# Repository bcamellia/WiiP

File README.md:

# WiiP
Circuits designed for usage in a portable Wii.  
See https://creationsofchris.wordpress.com/ for blog posts and design decisions.  

## Overview:  
* TPS5432 based power regulator takes a 5V input and outputs 1V, 1.15V, and 3.3V at up to 3A.
* LM485 based amp includes headphone sensing and uses a digital potentiometer for volume control.
* MAX4886 to connect Wii HDMI video (converted using GCVideo) to external monitor.
* Case designed in sketchup, prints ok using ABS plastic.

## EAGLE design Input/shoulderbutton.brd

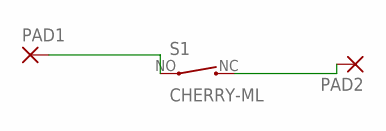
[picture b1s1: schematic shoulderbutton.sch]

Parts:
PAD1, PAD2: 2,15/1,0
S1: CHERRY-ML

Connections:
unnamed: PAD1.1, S1.NO (1)
unnamed: PAD2.1, S1.NC (2)

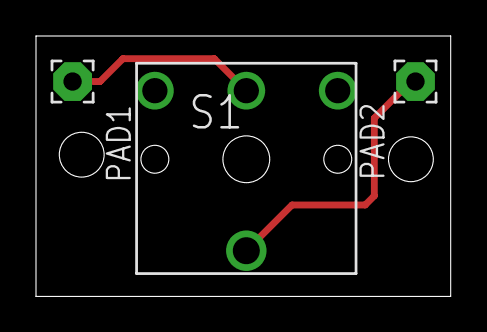
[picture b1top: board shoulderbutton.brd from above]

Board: 2 copper layers, 23.0 x 14.5 mm, 3 parts (0 on the bottom side), 2 nets.

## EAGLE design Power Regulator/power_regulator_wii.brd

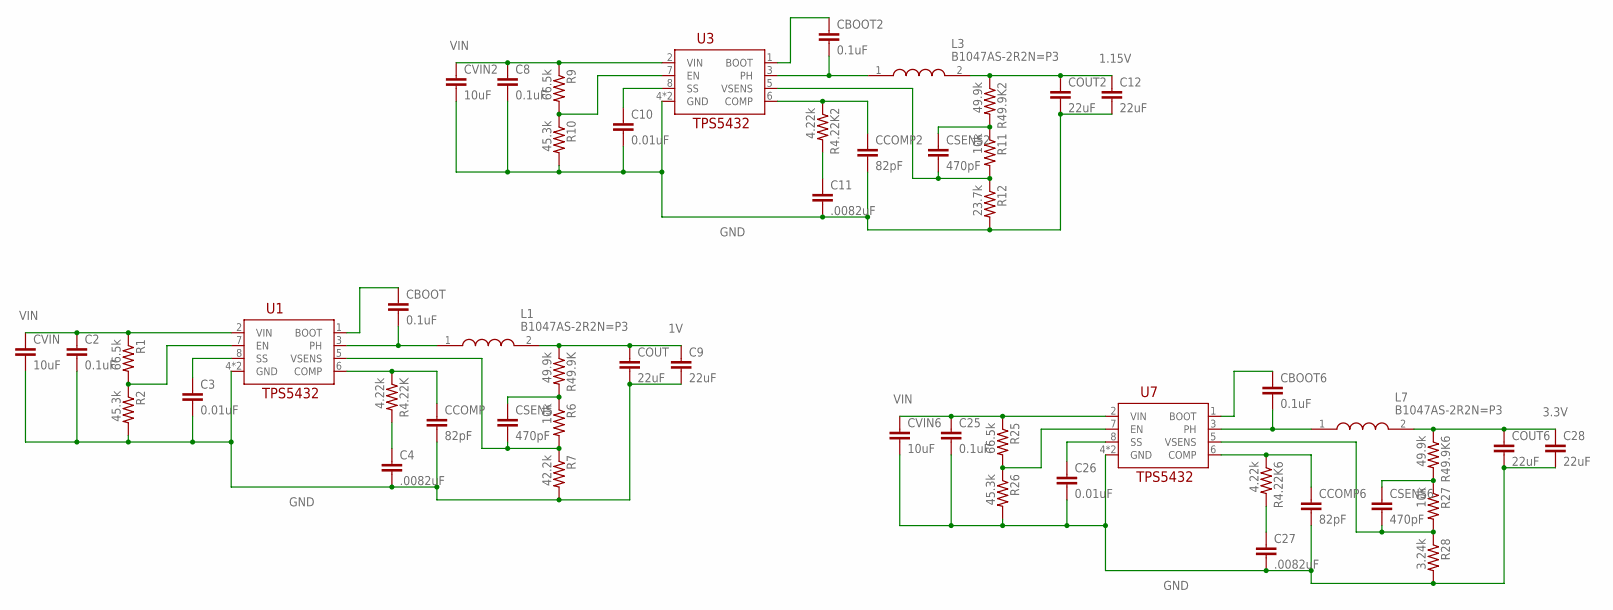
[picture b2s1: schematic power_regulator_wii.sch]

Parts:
C2, C8, C25: 0.1uF; C0603
C3, C10, C26: 0.01uF; C0603
C4, C11, C27: .0082uF; C0603
C9, C12, C28: 22uF; C0603
CBOOT, CBOOT2, CBOOT6: 0.1uF; C0603
CCOMP, CCOMP2, CCOMP6: 82pF; C0603
COUT, COUT2, COUT6: 22uF; C0603
CSENS, CSENS2, CSENS6: 470pF; C0603
CVIN, CVIN2, CVIN6: 10uF; C0603
L1, L3, L7: B1047AS-2R2N=P3; INDPM7474X500N
R1, R9, R25: 66.5k; R0603
R2, R10, R26: 45.3k; R0603
R4.22K, R4.22K2, R4.22K6: 4.22k; R0603
R6, R11, R27: 10k; R0603
R7: 42.2k; R0603
R12: 23.7k; R0603
R28: 3.24k; R0603
R49.9K, R49.9K2, R49.9K6: 49.9k; R0603
U1, U3, U7: TPS5432; SO-8

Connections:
1.15V: C12.1, COUT2.1, L3.2, R49.9K2.1
1V: C9.1, COUT.1, L1.2, R49.9K.1
3.3V: C28.1, COUT6.1, L7.2, R49.9K6.1
BOOT: CBOOT.1, U1.1 (BOOT)
BOOT2: CBOOT2.1, U3.1 (BOOT)
BOOT6: CBOOT6.1, U7.1 (BOOT)
COMP: CCOMP.1, R4.22K.1, U1.6 (COMP)
COMP2: CCOMP2.1, R4.22K2.1, U3.6 (COMP)
COMP6: CCOMP6.1, R4.22K6.1, U7.6 (COMP)
EN: R1.2, R2.1, U1.7 (EN)
EN2: R9.2, R10.1, U3.7 (EN)
EN6: R25.2, R26.1, U7.7 (EN)
GND: C2.2, C3.2, C4.2, C8.2, C9.2, C10.2, C11.2, C12.2, C25.2, C26.2, C27.2, C28.2, CCOMP.2, CCOMP2.2, CCOMP6.2, COUT.2, COUT2.2, COUT6.2, CVIN.2, CVIN2.2, CVIN6.2, R2.2, R7.2, R10.2, R12.2, R26.2, R28.2, U1.4 (GND), U1.PAD (GND), U3.4 (GND), U3.PAD (GND), U7.4 (GND), U7.PAD (GND)
unnamed: C11.1, R4.22K2.2
unnamed: CSENS2.1, R11.1, R49.9K2.2
unnamed: C4.1, R4.22K.2
unnamed: CSENS.1, R6.1, R49.9K.2
unnamed: C27.1, R4.22K6.2
unnamed: CSENS6.1, R27.1, R49.9K6.2
PH: CBOOT.2, L1.1, U1.3 (PH)
PH2: CBOOT2.2, L3.1, U3.3 (PH)
PH6: CBOOT6.2, L7.1, U7.3 (PH)
SS: C3.1, U1.8 (SS)
SS2: C10.1, U3.8 (SS)
SS6: C26.1, U7.8 (SS)
VIN: C2.1, C8.1, C25.1, CVIN.1, CVIN2.1, CVIN6.1, R1.1, R9.1, R25.1, U1.2 (VIN), U3.2 (VIN), U7.2 (VIN)
VSENS: CSENS.2, R6.2, R7.1, U1.5 (VSENS)
VSENS2: CSENS2.2, R11.2, R12.1, U3.5 (VSENS)
VSENS6: CSENS6.2, R27.2, R28.1, U7.5 (VSENS)

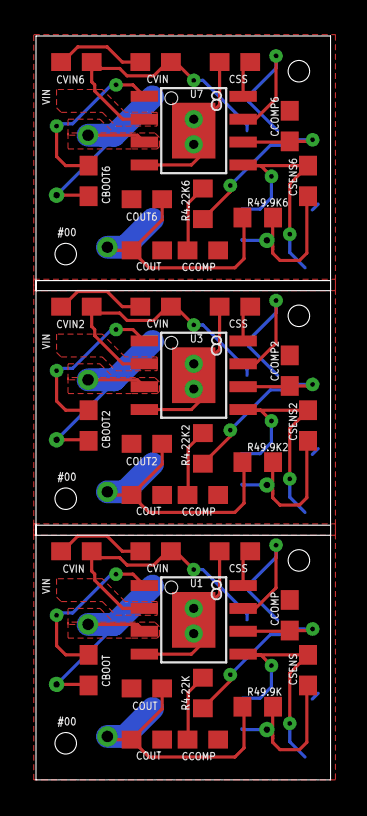
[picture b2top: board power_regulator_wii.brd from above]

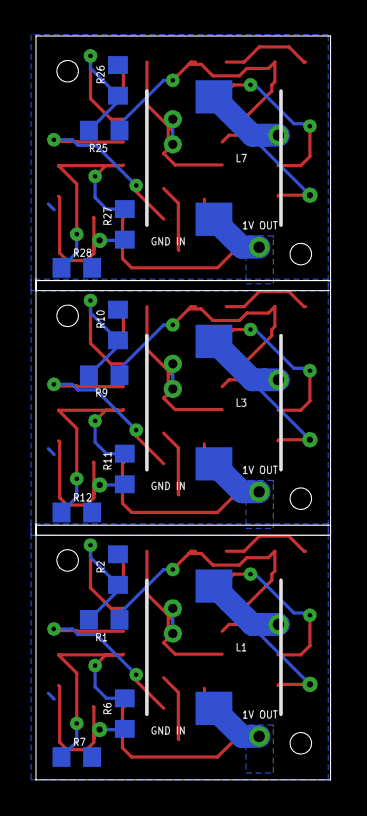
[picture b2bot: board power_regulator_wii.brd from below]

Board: 2 copper layers, 16.4 x 41.3 mm, 51 parts (15 on the bottom side), 29 nets.

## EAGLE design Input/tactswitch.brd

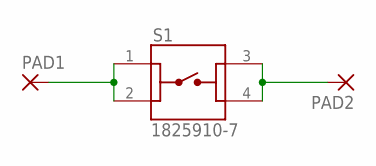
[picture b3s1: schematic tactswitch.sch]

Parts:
PAD1, PAD2: 2,15/1,0
S1: 1825910-7; SW_1825910-7

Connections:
unnamed: PAD1.1, S1.1, S1.2
unnamed: PAD2.1, S1.3, S1.4

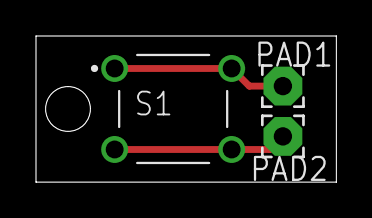
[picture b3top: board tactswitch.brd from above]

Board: 2 copper layers, 16.7 x 8.1 mm, 3 parts (0 on the bottom side), 2 nets.

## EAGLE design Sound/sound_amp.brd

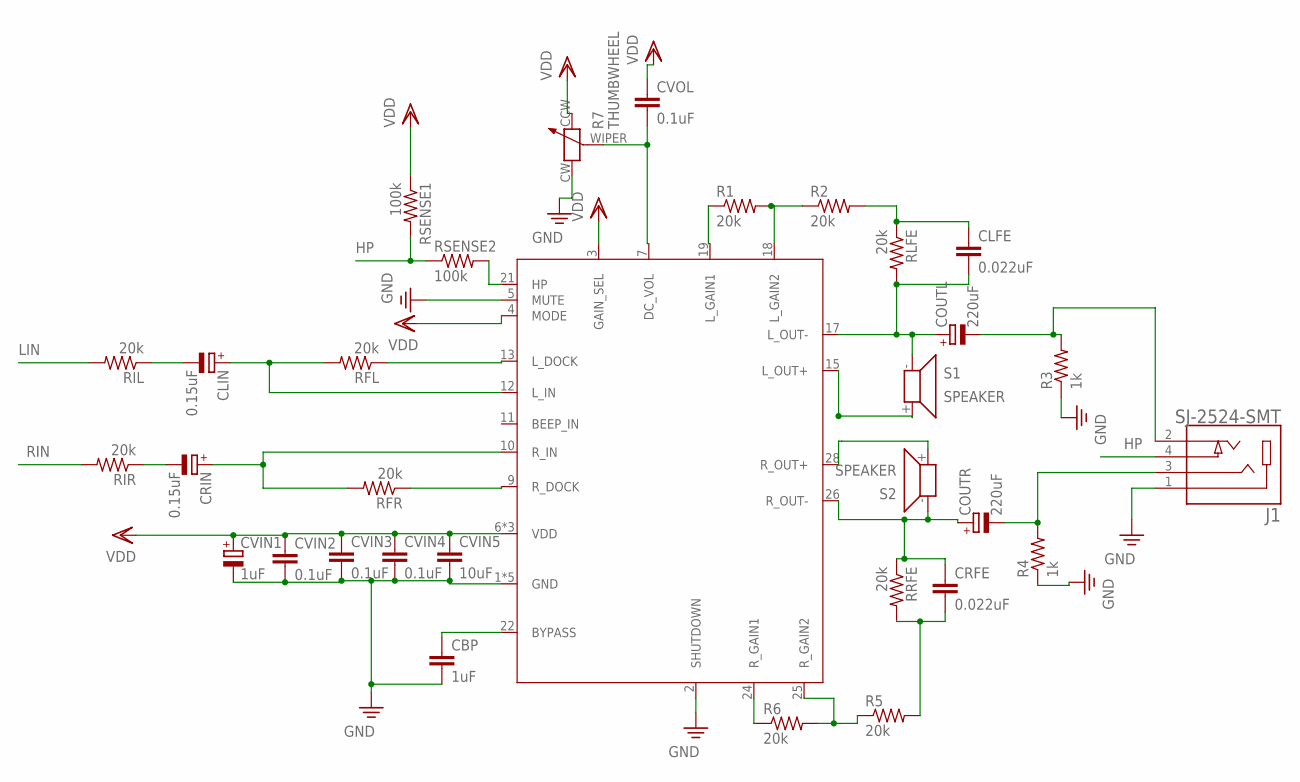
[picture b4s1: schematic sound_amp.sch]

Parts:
CBP: 1uF; C0603
CLFE: 0.022uF; C0603
CLIN: 0.15uF; B45181A
COUTL: 220uF; B45181A
COUTR: 220uF; B45181A
CRFE: 0.022uF; C0603
CRIN: 0.15uF; B45181A
CVIN1: 1uF; B45181A
CVIN2, CVIN3, CVIN4: 0.1uF; C0603
CVIN5: 10uF; C0603
CVOL: 0.1uF; C0603
J1: SJ-2524-SMT; CUI_SJ-2524-SMT
R1, R2, R5, R6: 20k; R0603
R3, R4: 1k; R0603
R7: THUMBWHEEL
RFL: 20k; R0603
RFR: 20k; R0603
RIL: 20k; R0603
RIR: 20k; R0603
RLFE: 20k; R0603
RRFE: 20k; R0603
RSENSE1, RSENSE2: 100k; R0603
S1, S2: SPEAKER; SIGNALOUT
U1: LM4835; TSSOP-28

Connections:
BYPASS: CBP.1, U1.22 (BYPASS)
GND: CBP.2, CVIN1.-, CVIN2.2, CVIN3.2, CVIN4.2, CVIN5.2, J1.1, R3.1, R4.1, R7.CW, U1.1 (GND), U1.2 (SHUTDOWN), U1.5 (MUTE), U1.8 (GND), U1.14 (GND), U1.20 (GND), U1.23 (GND)
HP: J1.4, RSENSE1.2, RSENSE2.1
LDOCK: RFL.1, U1.13 (L_DOCK)
LIN: RIL.2
LOUT+: S1.+, U1.15 (L_OUT+)
LOUT-: CLFE.2, COUTL.+, RLFE.2, S1.-, U1.17 (L_OUT-)
unnamed: CLIN.+, RFL.2, U1.12 (L_IN)
unnamed: CRIN.+, RFR.2, U1.10 (R_IN)
unnamed: CRIN.-, RIR.1
unnamed: CLIN.-, RIL.1
unnamed: CVOL.2, R7.WIPER, U1.7 (DC_VOL)
unnamed: RSENSE2.2, U1.21 (HP)
unnamed: CLFE.1, R2.2, RLFE.1
unnamed: R1.2, R2.1, U1.18 (L_GAIN2)
unnamed: R1.1, U1.19 (L_GAIN1)
unnamed: COUTL.-, J1.2, R3.2
unnamed: COUTR.-, J1.3, R4.2
unnamed: CRFE.2, R5.2, RRFE.2
RDOCK: RFR.1, U1.9 (R_DOCK)
RGAIN1: R6.1, U1.24 (R_GAIN1)
RGAIN2: R5.1, R6.2, U1.25 (R_GAIN2)
RIN: RIR.2
ROUT+: S2.+, U1.28 (R_OUT+)
ROUT-: COUTR.+, CRFE.1, RRFE.1, S2.-, U1.26 (R_OUT-)
VDD: CVIN1.+, CVIN2.1, CVIN3.1, CVIN4.1, CVIN5.1, CVOL.1, R7.CCW, RSENSE1.1, U1.3 (GAIN_SEL), U1.4 (MODE), U1.6 (VDD), U1.16 (VDD), U1.27 (VDD)

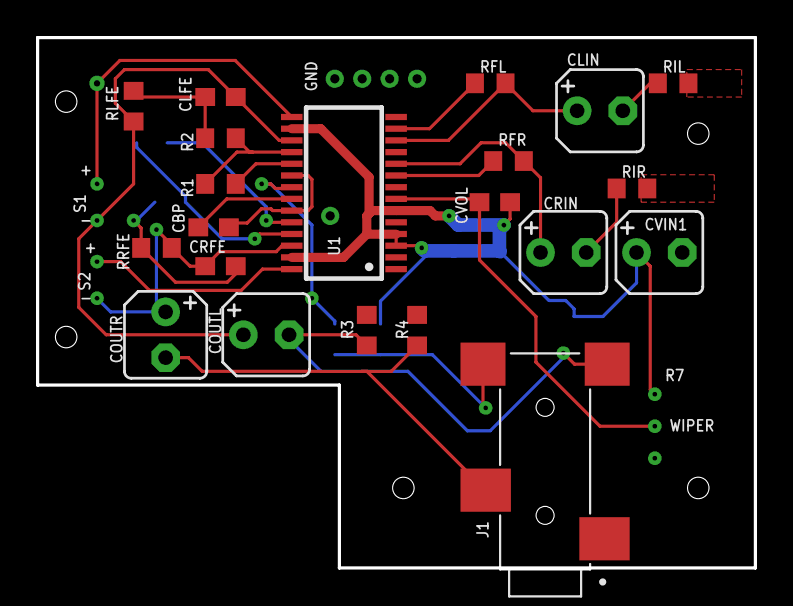
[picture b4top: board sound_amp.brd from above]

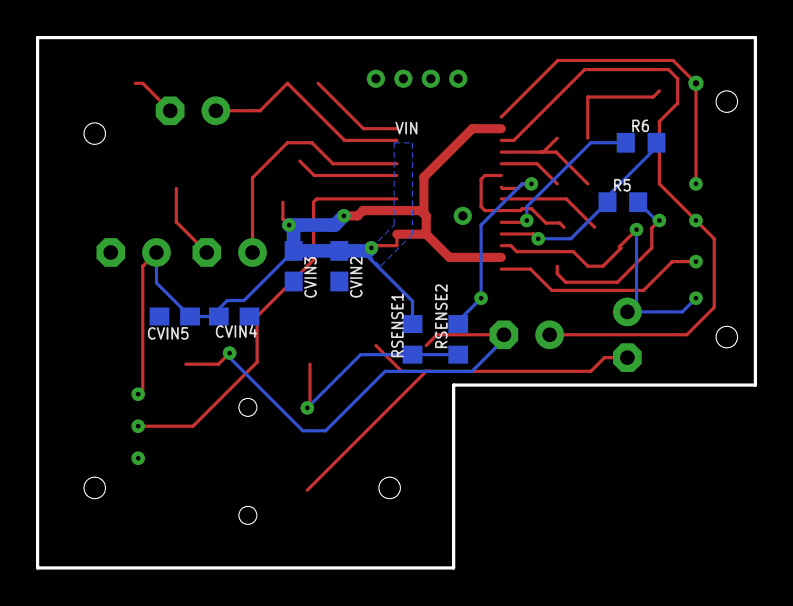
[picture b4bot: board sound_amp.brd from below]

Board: 2 copper layers, 39.9 x 29.5 mm, 32 parts (8 on the bottom side), 24 nets.

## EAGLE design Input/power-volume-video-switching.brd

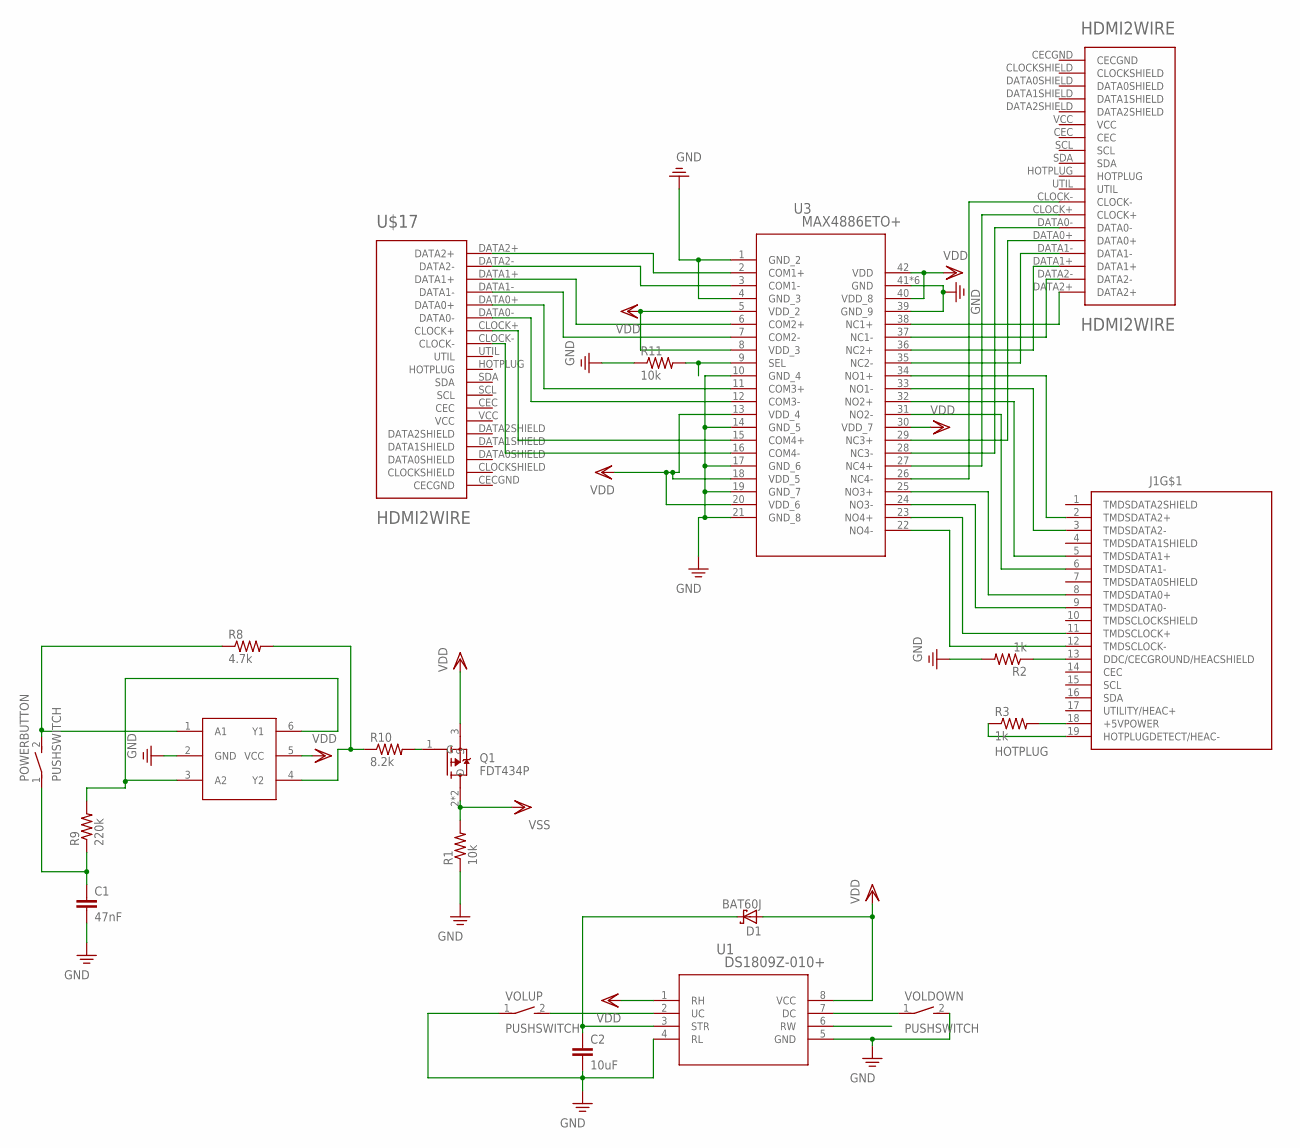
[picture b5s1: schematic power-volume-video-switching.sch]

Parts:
C1: 47nF; C0603
C2: 10uF; C0603
D1: BAT60J; SOD323_ST
HDMI2WIRE: HDMI2WIRE; HDMI
J1: 685119136923
POWERBUTTON: PUSHSWITCH
Q1: FDT434P; SOT230P700X180-4N
R1, R11: 10k; R0603
R2, R3: 1k; R0603
R8: 4.7k; R0603
R9: 220k; R0603
R10: 8.2k; R0603
U1: DS1809Z-010+; 21-0041B_8
U2: NC7WZ14P6X; SC70-6L
U3: MAX4886ETO+; 21-0181B_T423590M-1
U$17: HDMI2WIRE; HDMI
VOLDOWN: PUSHSWITCH
VOLUP: PUSHSWITCH

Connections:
HOTPLUG: J1.19 (HOTPLUGDETECT/HEAC-), R3.1, R11.2, U3.9 (SEL)
unnamed: C2.1, D1.C, U1.3 (STR)
unnamed: U1.2 (UC), VOLUP.2 (S)
unnamed: R9.2, U2.3 (A2), U2.6 (Y1)
unnamed: POWERBUTTON.2 (S), R8.1, U2.1 (A1)
unnamed: J1.2 (TMDSDATA2+), U3.34 (NO1+)
unnamed: U1.7 (DC), VOLDOWN.1
unnamed: J1.3 (TMDSDATA2-), U3.33 (NO1-)
unnamed: J1.5 (TMDSDATA1+), U3.32 (NO2+)
unnamed: R8.2, R10.1, U2.4 (Y2)
unnamed: J1.6 (TMDSDATA1-), U3.31 (NO2-)
unnamed: C1.1, POWERBUTTON.1, R9.1
unnamed: J1.8 (TMDSDATA0+), U3.25 (NO3+)
unnamed: J1.9 (TMDSDATA0-), U3.24 (NO3-)
unnamed: Q1.1 (G), R10.2
unnamed: J1.11 (TMDSCLOCK+), U3.23 (NO4+)
unnamed: J1.12 (TMDSCLOCK-), U3.22 (NO4-)
unnamed: U3.2 (COM1+), U$17.DATA2+
unnamed: J1.13 (DDC/CECGROUND/HEACSHIELD), R2.1
unnamed: U3.3 (COM1-), U$17.DATA2-
unnamed: J1.18 (+5VPOWER), R3.2
unnamed: U3.6 (COM2+), U$17.DATA1+
unnamed: U3.7 (COM2-), U$17.DATA1-
unnamed: U3.11 (COM3+), U$17.DATA0+
unnamed: U3.12 (COM3-), U$17.DATA0-
unnamed: U3.15 (COM4+), U$17.CLOCK+
unnamed: U3.16 (COM4-), U$17.CLOCK-
unnamed: HDMI2WIRE.DATA2+, U3.38 (NC1+)
unnamed: HDMI2WIRE.DATA2-, U3.37 (NC1-)
unnamed: HDMI2WIRE.DATA1+, U3.36 (NC2+)
unnamed: HDMI2WIRE.DATA1-, U3.35 (NC2-)
unnamed: HDMI2WIRE.DATA0+, U3.29 (NC3+)
unnamed: HDMI2WIRE.DATA0-, U3.28 (NC3-)
unnamed: HDMI2WIRE.CLOCK+, U3.27 (NC4+)
unnamed: HDMI2WIRE.CLOCK-, U3.26 (NC4-)
PE: C1.2, C2.2, R1.1, R2.2, R11.1, U1.4 (RL), U1.5 (GND), U2.2 (GND), U3.1 (GND_2), U3.4 (GND_3), U3.10 (GND_4), U3.14 (GND_5), U3.17 (GND_6), U3.19 (GND_7), U3.21 (GND_8), U3.39 (GND_9), U3.41 (GND), U3.43 (GND), U3.P$1 (GND), U3.P$2 (GND), U3.P$3 (GND), U3.P$4 (GND), VOLDOWN.2 (S), VOLUP.1
VDD: D1.A, Q1.3 (S), U1.1 (RH), U1.8 (VCC), U2.5 (VCC), U3.5 (VDD_2), U3.8 (VDD_3), U3.13 (VDD_4), U3.18 (VDD_5), U3.20 (VDD_6), U3.30 (VDD_7), U3.40 (VDD_8), U3.42 (VDD)
VSS: Q1.2 (D), Q1.4 (D), R1.2
WIPER: U1.6 (RW)

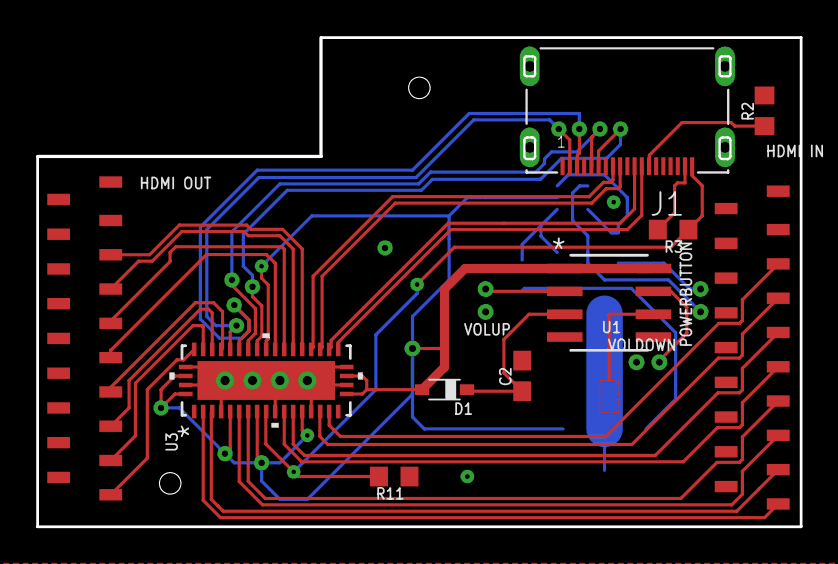
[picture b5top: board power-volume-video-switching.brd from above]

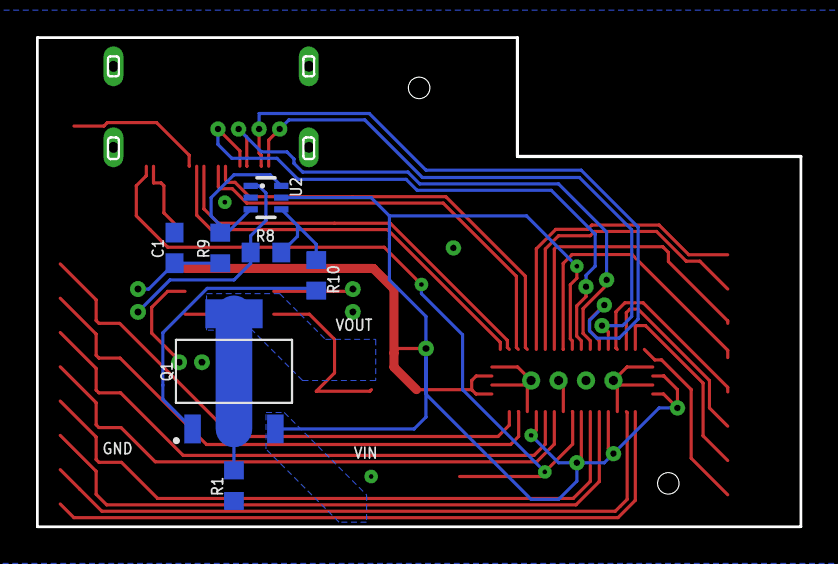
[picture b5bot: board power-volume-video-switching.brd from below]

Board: 2 copper layers, 42.4 x 27.2 mm, 20 parts (9 on the bottom side), 38 nets.

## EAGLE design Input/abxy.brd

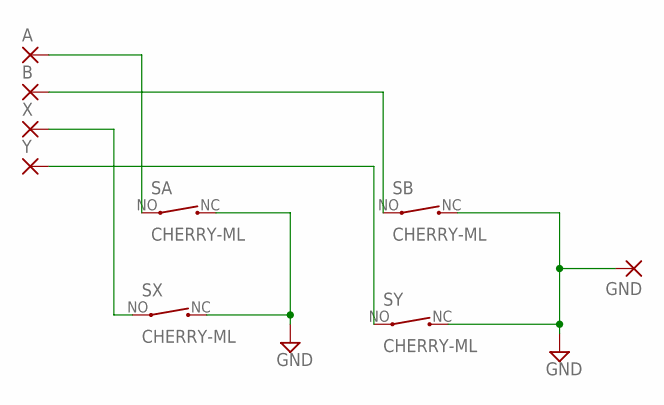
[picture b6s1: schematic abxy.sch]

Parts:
A: 3,81/1,3
B: 3,81/1,3
GND: 2,15/1,0
SA: CHERRY-ML
SB: CHERRY-ML
SX: CHERRY-ML
SY: CHERRY-ML
X: 3,81/1,3
Y: 3,81/1,3

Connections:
GND: GND.1, SA.NC (2), SB.NC (2), SX.NC (2), SY.NC (2)
unnamed: A.1, SA.NO (1)
unnamed: B.1, SB.NO (1)
unnamed: SX.NO (1), X.1
unnamed: SY.NO (1), Y.1

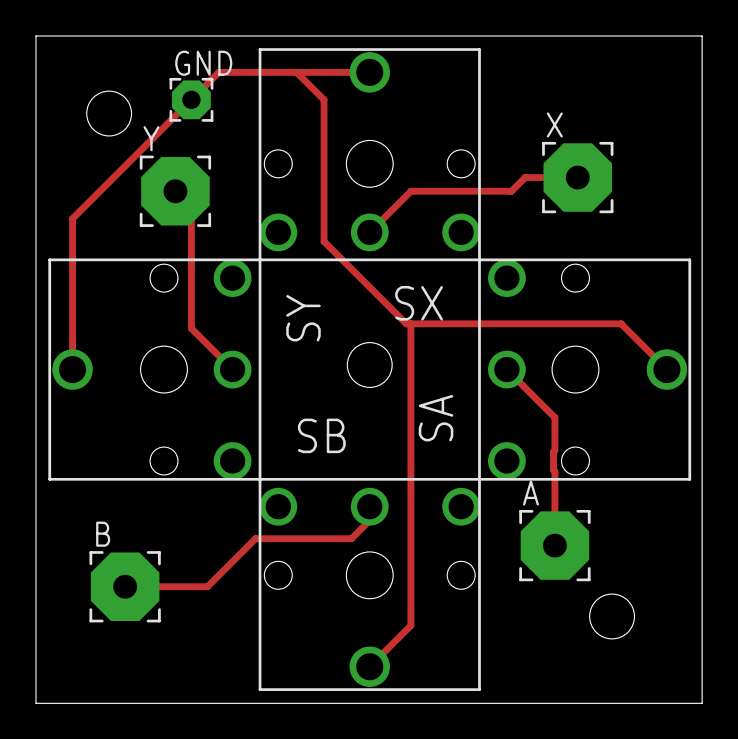
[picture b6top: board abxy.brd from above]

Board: 2 copper layers, 37.0 x 37.1 mm, 9 parts (0 on the bottom side), 5 nets.

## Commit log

2020-06-19 Add Circuits/PCBs/3D Models
    Added circuits and PCBs for input, sound, power regulation, and Aurelio's GCPlus as a custom gamecube controller. Also added models for the top and bottom halves of the case with a rough layout of po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

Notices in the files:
parts and their libraries:
InputOutputIO: Copyright: Würth Elektronik
